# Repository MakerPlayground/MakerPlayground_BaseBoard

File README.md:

# MakerPlayground_BaseBoard
Maker Playground Base Board schematic and PCB design.

Complete the design with Kicad 5.0.2 or newer.

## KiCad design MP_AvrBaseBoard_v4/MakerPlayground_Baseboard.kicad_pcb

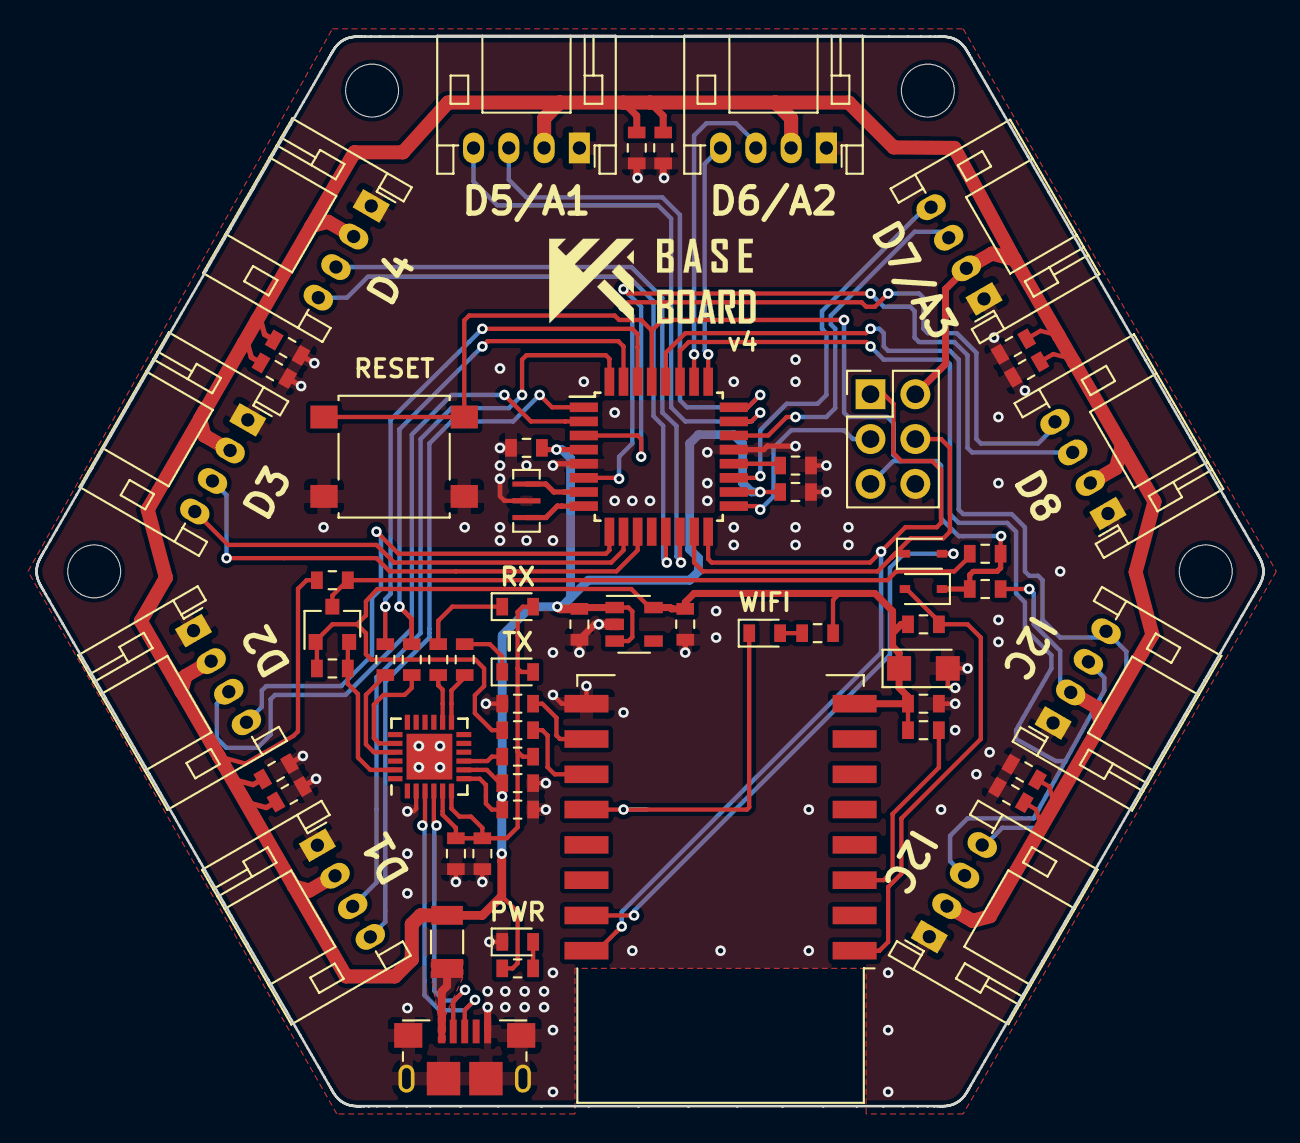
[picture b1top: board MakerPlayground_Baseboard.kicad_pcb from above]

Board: 2 copper layers, 69.5 x 60.6 mm, 63 parts (1 on the bottom side), 51 nets.

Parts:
C1, C2: 4.7uF; C_0603_1608Metric
C3, C5, C7, C11, C12, C13, C15, C16, C18, C20, C22: 0.1uF; C_0603_1608Metric
C4, C9, C17, C19, C21: 10uF; C_0603_1608Metric
C6, C8, C14: 1uF; C_0603_1608Metric
C10: 10uF; CP_EIA-3216-12_Kemet-S
D2: Green; LED_0603_1608Metric
D3, D4: Yellow; LED_0603_1608Metric
D5, D7: 1SS355VMTE-17; D_SOD-323
D6: RED; LED_0603_1608Metric
F1: 6V/0.5A; Fuse_1206_3216Metric
J2: USB_B_Micro; USB_Micro-B_Amphenol_10118193_Horizontal
J3: AVR-ISP-6; PinHeader_2x03_P2.54mm_Vertical
J4, J5, J6, J7, J8, J9, J10, J11, J13, J14: 112504RT/RH; JST_PH_S4B-PH-K_1x04_P2.00mm_Horizontal
JP1: Flashing Mode; SolderJumper-2_P1.3mm_Open_Pad1.0x1.5mm
Q2: BSS138; SOT-23
R2, R5, R6, R7, R8, R9, R14: 1K; R_0603_1608Metric
R3, R4, R10, R11, R12, R13, R15: 10K; R_0603_1608Metric
SW1: RESET; SW_SPST_B3S-1000
U2: AP2127K-3.3; SOT-23-5
U3: CP2102N-A01-GQFN24; QFN-24-1EP_4x4mm_P0.5mm_EP2.6x2.6mm
U4: ATmega328PB-MU; TQFP-32_7x7mm_P0.8mm
U5: ESP-12E; ESP-12E_ButtLess
Y1: CSTCE16M0V53-R0; Resonator_Murata_CSTCE-V-3Pin_3.2x1.3mm

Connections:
+3V3: C8.1, C10.1, C14.1, Q2.1, R3.1, R10.2, R11.1, R13.1, R14.1, U2.5, U5.8
+5V: C2.1, C4.1, C5.1, C6.1, C7.1, C9.1, C11.1, C13.1, C16.1, C17.1, C18.1, C19.1, C20.1, C21.1, C22.1, F1.1, J3.2, J4.2, J5.2, J6.2, J7.2, J8.2, J9.2, J10.2, J11.2, J13.2, J14.2, R4.1, R5.1, R15.1, U2.1, U2.3, U3.7, U3.8, U4.4, U4.18
/D+: J2.3, U3.3
/D-: J2.2, U3.4
A0: J5.4, U4.23
A1: J5.3, U4.24
A2: J8.4, U4.25
A3: J8.3, U4.26
A4: J11.4, U4.19
A5: J11.3, U4.22
D2: J4.3, U4.32
D3: J4.4, U4.1
D4: J7.3, U4.2
D5: J7.4, U4.9
D6: J10.4, U4.10
D7: J10.3, U4.11
D9: J13.4, U4.13
D10: J13.3, U4.14
D11: J14.3, U4.3
D12: J14.4, U4.6
DTR: C15.1, Q2.3, R4.2
DTR_3V3: Q2.2, R3.2, U3.23
ESP_RX: D7.1, J3.4, U4.15
ESP_TX: J3.1, U4.16, U5.22
GND: C1.2, C2.2, C3.2, C4.2, C5.2, C6.2, C7.2, C8.2, C9.2, C10.2, C11.2, C12.2, C13.2, C14.2, C16.2, C17.2, C18.2, C19.2, C20.2, C21.2, C22.2, D2.1, J2.5, J2.6, J3.6, J4.1, J5.1, J6.1, J7.1, J8.1, J9.1, J10.1, J11.1, J13.1, J14.1, JP1.2, R12.1, SW1.2, U2.2, U3.2, U3.25, U4.5, U4.21, U5.15, Y1.2
MCU_RX: R7.1, U4.30
MCU_TX: R6.1, U4.31
unnamed: C1.1, C3.1, D3.2, D4.2, R2.1, U3.5, U3.6
unnamed: C12.1, U4.20
unnamed: D2.2, R5.2
unnamed: D3.1, R8.1
unnamed: D4.1, R9.1
unnamed: D5.2, R11.2, U5.1
unnamed: D6.1, JP1.1, U5.18
unnamed: D6.2, R14.2
unnamed: D7.2, U5.21
unnamed: F1.2, J2.1
unnamed: R2.2, U3.9
unnamed: R6.2, U3.20
unnamed: R7.2, U3.21
unnamed: R8.2, U3.13
unnamed: R9.2, U3.14
unnamed: R10.1, U5.3
unnamed: R12.2, U5.16
unnamed: R13.2, U5.17
unnamed: U4.7, Y1.3
unnamed: U4.8, Y1.1
RST: C15.2, D5.1, J3.5, R15.2, SW1.1, U4.29
SCK: J3.3, U4.17
SCL0: J6.4, J9.4, U4.28
SDA0: J6.3, J9.3, U4.27

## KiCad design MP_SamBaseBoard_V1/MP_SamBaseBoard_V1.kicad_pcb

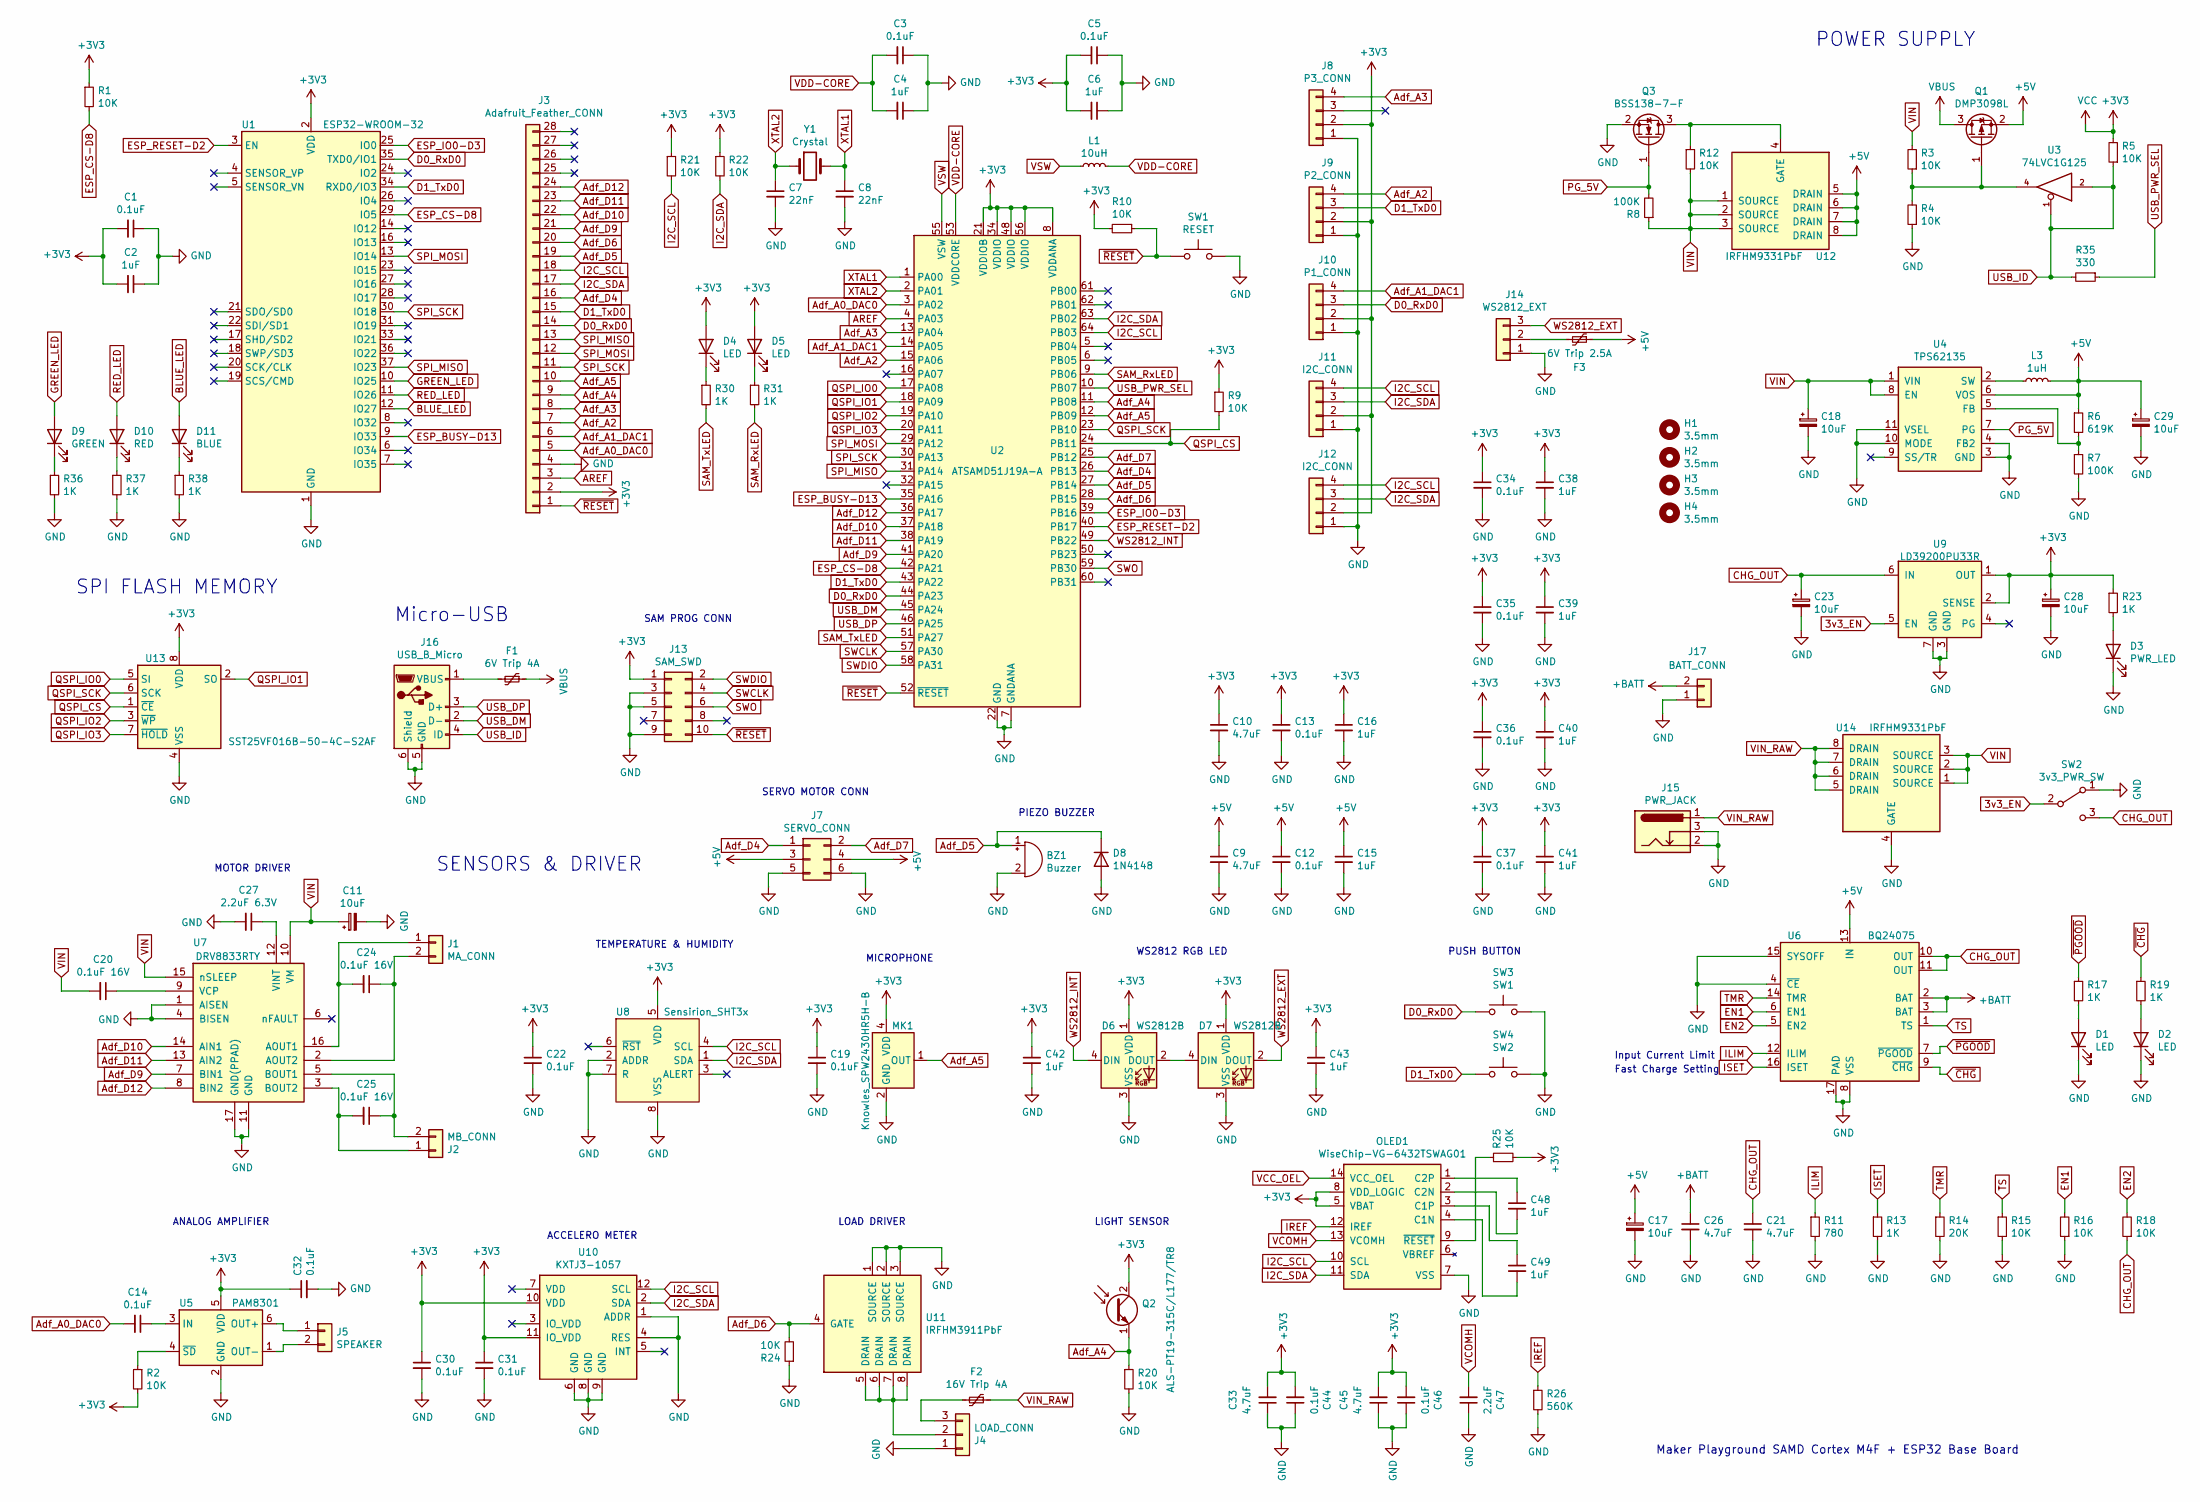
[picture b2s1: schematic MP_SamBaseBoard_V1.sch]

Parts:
BZ1: Buzzer; MagneticBuzzer_Kobitone_254-EMB84Q-RO
C1, C3, C5, C12, C13, C14, C19, C22, C30, C31, C32, C34, C35, C36, C37, C44, C46: 0.1uF; C_0603_1608Metric
C2, C4, C6, C15, C16, C38, C39, C40, C41, C42, C43, C48, C49: 1uF; C_0603_1608Metric
C7, C8: 22nF; C_0603_1608Metric; Mfg. Part 06036C223KAT2A
C9, C10, C21, C26, C33, C45: 4.7uF; C_0603_1608Metric
C11, C17, C18, C23, C28, C29: 10uF; CP_EIA-3216-12_Kemet-S
C20, C24, C25: 0.1uF 16V; C_0603_1608Metric
C27: 2.2uF 6.3V; C_0603_1608Metric
C47: 2.2uF; C_0603_1608Metric
D1, D2, D4, D5: LED; LED_0603_1608Metric
D3: PWR_LED; LED_0603_1608Metric
D6, D7: WS2812B; WS2812B_MINI
D8: 1N4148; D_SOD-323
D9: GREEN; LED_0603_1608Metric
D10: RED; LED_0603_1608Metric
D11: BLUE; LED_0603_1608Metric
F1: 6V Trip 4A; Fuse_1206_3216Metric; Mfg Part TLC-NSMD200
F2: 16V Trip 4A; Fuse_1812_4532Metric; Mfg Part SMD1812P200TF16
F3: 6V Trip 2.5A; Fuse_1812_4532Metric; Mfg Part MF-MSMF125-2
H1, H2, H3, H4: 3.5mm; MountingHole_3.5mm
J1: MA_CONN; TerminalBlock_Dinkle_ED350V_1x02_P3.50mm_Horizontal
J2: MB_CONN; TerminalBlock_Dinkle_ED350V_1x02_P3.50mm_Horizontal
J3: Adafruit_Feather_CONN; Adafruit-Feather_WoMountPoint_TypeB
J4: LOAD_CONN; TerminalBlock_Dinkle_ED350V_1x03_P3.50mm_Horizontal
J5: SPEAKER; TerminalBlock_Dinkle_ED350V_1x02_P3.50mm_Horizontal
J7: SERVO_CONN; PinHeader_2x03_P2.54mm_Vertical
J8: P3_CONN; JST_PH_B4B-PH-K_1x04_P2.00mm_Vertical
J9: P2_CONN; JST_PH_B4B-PH-K_1x04_P2.00mm_Vertical
J10: P1_CONN; JST_PH_B4B-PH-K_1x04_P2.00mm_Vertical
J11, J12: I2C_CONN; JST_PH_B4B-PH-K_1x04_P2.00mm_Vertical
J13: SAM_SWD; PinHeader_2x05_P1.27mm_Vertical
J14: WS2812_EXT; PinHeader_1x03_P2.54mm_Vertical
J15: PWR_JACK; BarrelJack_Horizontal; Mfg. Part PJ-002A; Mouser No. 490-PJ-002A
J16: USB_B_Micro; USB_Micro-B_Amphenol_10118193_Horizontal
J17: BATT_CONN; TerminalBlock_Dinkle_ED350V_1x02_P3.50mm_Horizontal
L1: 10uH; L_0805_2012Metric; Mfg. Part LQM21DH100M70L
L3: 1uH; SPM6530T; Mfg. Part SPM6530T-1R0M120
MK1: Knowles_SPW2430HR5H-B; SPW2430HR5H-B
OLED1: WiseChip-VG-6432TSWAG01
Q1: DMP3098L; SOT-23
Q2: ALS-PT19-315C/L177/TR8; D_0603_1608Metric
Q3: BSS138-7-F; SOT-23
R1, R2, R3, R4, R5, R9, R10, R12, R15, R16, R18, R20, R21, R22, R24, R25: 10K; R_0603_1608Metric
R6: 619K; R_0603_1608Metric
R7, R8: 100K; R_0603_1608Metric
R11: 780; R_0603_1608Metric
R13, R17, R19, R23, R30, R31, R36, R37, R38: 1K; R_0603_1608Metric
R14: 20K; R_0603_1608Metric
R26: 560K; R_0603_1608Metric
R35: 330; R_0603_1608Metric
SW1: RESET; SW_Push_TS-1145A-B-A
SW2: 3v3_PWR_SW; SSSS811101
SW3: SW1; SW_Push_TS-1145A-B-A
SW4: SW2; SW_Push_TS-1145A-B-A
U1: ESP32-WROOM-32; ESP32-WROOM-32_WifiNinaPin
U2: ATSAMD51J19A-A; TQFP-64_10x10mm_P0.5mm
U3: 74LVC1G125; SOT-23-5
U4: TPS62135; VQFN-HR-11
U5: PAM8301; SOT-23-6
U6: BQ24075; VQFN-16-1EP_3x3mm_P0.5mm_EP1.6x1.6mm_ThermalVias
U7: DRV8833RTY; Texas_S-PWQFN-N16_EP2.1x2.1mm_ThermalVias
U8: Sensirion_SHT3x
U9: LD39200PU33R; DFN-6-1EP_3x3mm_P0.95mm_EP1.7x2.6mm
U10: KXTJ3-1057; LGA-12_2x2mm_P0.5mm
U11: IRFHM3911PbF; PQFN_3x3mm_IRFHM3911PbF
U12, U14: IRFHM9331PbF; PQFN_3x3mm_IRFHM9331TRPbF
U13: SST25VF016B-50-4C-S2AF; SOIC-8_5.275x5.275mm_P1.27mm
Y1: Crystal; Crystal_SMD_2012-2Pin_2.0x1.2mm; Mfg. Part ABS06-127-32.768kHz-T

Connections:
3v3_EN: SW2.2 (B), U9.5 (EN)
+3V3: C1.2, C2.2, C5.2, C6.2, C10.1, C13.1, C16.1, C19.1, C22.1, C28.1, C30.1, C31.1, C32.1, C33.2, C34.1, C35.1, C36.1, C37.1, C38.1, C39.1, C40.1, C41.1, C42.1, C43.1, C44.2, C45.2, C46.2, D4.2 (A), D5.2 (A), D6.1 (VDD), D7.1 (VDD), J3.2, J8.2, J9.2, J10.2, J11.2, J12.2, J13.1, MK1.4 (VDD), OLED1.5 (VBAT), OLED1.8 (VDD_LOGIC), Q2.2 (C), R1.1, R2.2, R5.2, R9.1, R10.2, R21.1, R22.1, R23.1, R25.2, U1.2 (VDD), U2.8 (VDDANA), U2.21 (VDDIOB), U2.34 (VDDIO), U2.48 (VDDIO), U2.56 (VDDIO), U3.5 (VCC), U5.5 (VDD), U8.5 (VDD), U9.1 (OUT), U9.2 (SENSE), U10.10 (VDD), U10.11 (IO_VDD), U13.8 (VDD)
+5V: C9.1, C12.1, C15.1, C17.1, C29.1, F3.1, J7.3, J7.4, L3.2, Q1.2 (S), R6.1, U4.6 (VOS), U6.13 (IN), U12.5 (DRAIN), U12.6 (DRAIN), U12.7 (DRAIN), U12.8 (DRAIN)
+BATT: C26.1, J17.2, U6.2 (BAT), U6.3 (BAT)
AREF: J3.3, U2.4 (PA03)
Adf_A0_DAC0: C14.2, J3.5, U2.3 (PA02)
Adf_A1_DAC1: J3.6, J10.4, U2.14 (PA05)
Adf_A2: J3.7, J9.4, U2.15 (PA06)
Adf_A3: J3.8, J8.4, U2.13 (PA04)
Adf_A4: J3.9, Q2.1 (E), R20.1, U2.11 (PB08)
Adf_A5: J3.10, MK1.1 (OUT), U2.12 (PB09)
Adf_D4: J3.16, J7.1, U2.26 (PB13)
Adf_D5: BZ1.1 (-), D8.1 (K), J3.19, U2.27 (PB14)
Adf_D6: J3.20, R24.2, U2.28 (PB15), U11.4 (GATE)
Adf_D7: J7.2, U2.25 (PB12)
Adf_D9: J3.21, U2.41 (PA20), U7.7 (BIN1)
Adf_D10: J3.22, U2.37 (PA18), U7.14 (AIN1)
Adf_D11: J3.23, U2.38 (PA19), U7.13 (AIN2)
Adf_D12: J3.24, U2.36 (PA17), U7.8 (BIN2)
BLUE_LED: D11.2 (A), U1.12 (IO27)
CHG_OUT: C21.1, C23.1, R18.1, SW2.3 (C), U6.10 (OUT), U6.11 (OUT), U9.6 (IN)
D0_RxD0: J3.14, J10.3, SW3.1, U1.35 (TXD0/IO1), U2.44 (PA23)
D1_TxD0: J3.15, J9.3, SW4.1, U1.34 (RXD0/IO3), U2.43 (PA22)
EN1: R16.2, U6.6 (EN1)
EN2: R18.2, U6.5 (EN2)
ESP_BUSY-D13: U1.9 (IO33), U2.35 (PA16)
ESP_CS-D8: R1.2, U1.29 (IO5), U2.42 (PA21)
ESP_IO0-D3: U1.25 (IO0), U2.39 (PB16)
ESP_RESET-D2: U1.3 (EN), U2.40 (PB17)
GND: BZ1.2 (+), C1.1, C2.1, C3.1, C4.1, C5.1, C6.1, C7.2, C8.2, C9.2, C10.2, C11.2, C12.2, C13.2, C15.2, C16.2, C17.2, C18.2, C19.2, C21.2, C22.2, C23.2, C26.2, C27.2, C28.2, C29.2, C30.2, C31.2, C32.2, C33.1, C34.2, C35.2, C36.2, C37.2, C38.2, C39.2, C40.2, C41.2, C42.2, C43.2, C44.1, C45.1, C46.1, C47.1, D1.1 (K), D2.1 (K), D3.1 (K), D6.3 (VSS), D7.3 (VSS), D8.2 (A), J3.4, J4.1, J7.5, J7.6, J8.1, J9.1, J10.1, J11.1, J12.1, J13.3, J13.5, J13.9, J14.1, J15.2, J15.3, J16.5 (GND), J16.6 (Shield), J17.1, MK1.2 (GND), MK1.3 (GND), OLED1.7 (VSS), Q3.2 (S), R4.1, R7.2, R11.2, R13.2, R14.2, R15.2, R16.1, R20.2, R24.1, R26.2, R36.2, R37.2, R38.2, SW1.2, SW2.1 (A), SW3.2, SW4.2, U1.1 (GND), U1.15 (GND), U1.38 (GND), U1.39 (GND), U2.7 (GNDANA), U2.22 (GND), U2.33 (GND), U2.47 (GND), U2.54 (GND), U3.3 (GND), U4.3 (GND), U4.4 (FB2), U4.10 (MODE), U4.11 (VSEL), U5.2 (GND), U6.4 (~CE), U6.8 (VSS), U6.15 (SYSOFF), U6.17 (PAD), U7.1 (AISEN), U7.4 (BISEN), U7.11 (GND), U7.17 (GND(PPAD)), U8.2 (ADDR), U8.7 (R), U8.8 (VSS), U8.9 (PAD), U9.3 (GND), U9.7 (GND), U10.1 (ADDR), U10.4 (RES), U10.6 (GND), U10.8 (GND), U10.9 (GND), U11.1 (SOURCE), U11.2 (SOURCE), U11.3 (SOURCE), U13.4 (VSS), U14.4 (GATE)
GREEN_LED: D9.2 (A), U1.10 (IO25)
I2C_SCL: J3.18, J11.4, J12.4, OLED1.10 (SCL), R21.2, U2.64 (PB03), U8.4 (SCL), U10.12 (SCL)
I2C_SDA: J3.17, J11.3, J12.3, OLED1.11 (SDA), R22.2, U2.63 (PB02), U8.1 (SDA), U10.2 (SDA)
ILIM: R11.1, U6.12 (ILIM)
IREF: OLED1.12 (IREF), R26.1
ISET: R13.1, U6.16 (ISET)
unnamed: C14.1, U5.3 (IN)
unnamed: C20.1, U7.9 (VCP)
unnamed: C24.1, J1.2, U7.2 (AOUT2)
unnamed: C24.2, J1.1, U7.16 (AOUT1)
unnamed: C25.1, J2.2, U7.5 (BOUT1)
unnamed: C25.2, J2.1, U7.3 (BOUT2)
unnamed: C27.1, U7.12 (VINT)
unnamed: C48.1, OLED1.1 (C2P)
unnamed: C48.2, OLED1.2 (C2N)
unnamed: C49.1, OLED1.3 (C1P)
unnamed: C49.2, OLED1.4 (C1N)
unnamed: D1.2 (A), R17.2
unnamed: D2.2 (A), R19.2
unnamed: D3.2 (A), R23.2
unnamed: D4.1 (K), R30.1
unnamed: D5.1 (K), R31.1
unnamed: D6.2 (DOUT), D7.4 (DIN)
unnamed: D9.1 (K), R36.1
unnamed: D10.1 (K), R37.1
unnamed: D11.1 (K), R38.1
unnamed: F1.2, J16.1 (VBUS)
unnamed: F2.2, J4.3
unnamed: F3.2, J14.2
unnamed: J4.2, U11.5 (DRAIN), U11.6 (DRAIN), U11.7 (DRAIN), U11.8 (DRAIN)
unnamed: J5.1, U5.6 (OUT+)
unnamed: J5.2, U5.1 (OUT-)
unnamed: L3.1, U4.2 (SW)
unnamed: OLED1.9 (~RESET), R25.1
unnamed: Q1.1 (G), R3.1, R4.2, U3.4
unnamed: Q3.3 (D), R12.1, U12.4 (GATE)
unnamed: R2.1, U5.4 (~SD)
unnamed: R6.2, R7.1, U4.5 (FB)
PG_5V: Q3.1 (G), R8.2, U4.7 (PG)
QSPI_CS: R9.2, U2.24 (PB11), U13.1 (~CE)
QSPI_IO0: U2.17 (PA08), U13.5 (SI)
QSPI_IO1: U2.18 (PA09), U13.2 (SO)
QSPI_IO2: U2.19 (PA10), U13.3 (~WP~)
QSPI_IO3: U2.20 (PA11), U13.7 (~HOLD~)
QSPI_SCK: U2.23 (PB10), U13.6 (SCK)
RED_LED: D10.2 (A), U1.11 (IO26)
SAM_RxLED: R31.2, U2.9 (PB06)
SAM_TxLED: R30.2, U2.51 (PA27)
SPI_MISO: J3.13, U1.37 (IO23), U2.31 (PA14)
SPI_MOSI: J3.12, U1.13 (IO14), U2.29 (PA12)
SPI_SCK: J3.11, U1.30 (IO18), U2.30 (PA13)
SWCLK: J13.4, U2.57 (PA30)
SWDIO: J13.2, U2.58 (PA31)
SWO: J13.6, U2.59 (PB30)
TMR: R14.1, U6.14 (TMR)
TS: R15.1, U6.1 (TS)
USB_DM: J16.2 (D-), U2.45 (PA24)
USB_DP: J16.3 (D+), U2.46 (PA25)
USB_ID: J16.4 (ID), R5.1, R35.2, U3.1, U3.2
USB_PWR_SEL: R35.1, U2.10 (PB07)
VBUS: F1.1, Q1.3 (D)
VCOMH: C47.2, OLED1.13 (VCOMH)
VDD-CORE: C3.2, C4.2, L1.2, U2.53 (VDDCORE)
VIN: C11.1, C18.1, C20.2, R3.2, R8.1, R12.2, U4.1 (VIN), U4.8 (EN), U7.10 (VM), U7.15 (nSLEEP), U12.1 (SOURCE), U12.2 (SOURCE), U12.3 (SOURCE), U14.1 (SOURCE), U14.2 (SOURCE), U14.3 (SOURCE)
VIN_RAW: F2.1, J15.1, U14.5 (DRAIN), U14.6 (DRAIN), U14.7 (DRAIN), U14.8 (DRAIN)
VSW: L1.1, U2.55 (VSW)
WS2812_EXT: D7.2 (DOUT), J14.3
WS2812_INT: D6.4 (DIN), U2.49 (PB22)
XTAL1: C8.1, U2.1 (PA00), Y1.2
XTAL2: C7.1, U2.2 (PA01), Y1.1
~CHG: R19.1, U6.9 (~CHG)
~PGOOD: R17.1, U6.7 (~PGOOD)
~RESET: J3.1, J13.10, R10.1, SW1.1, U2.52 (~RESET)

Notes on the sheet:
POWER SUPPLY
SENSORS & DRIVER
ACCELERO METER
TEMPERATURE & HUMIDITY
MOTOR DRIVER
ANALOG AMPLIFIER
LOAD DRIVER
MICROPHONE
Maker Playground SAMD Cortex M4F + ESP32 Base Board
PIEZO BUZZER
SPI FLASH MEMORY
Fast Charge Setting
Input Current Limit
Micro-USB
SERVO MOTOR CONN
SAM PROG CONN
WS2812 RGB LED
LIGHT SENSOR
PUSH BUTTON

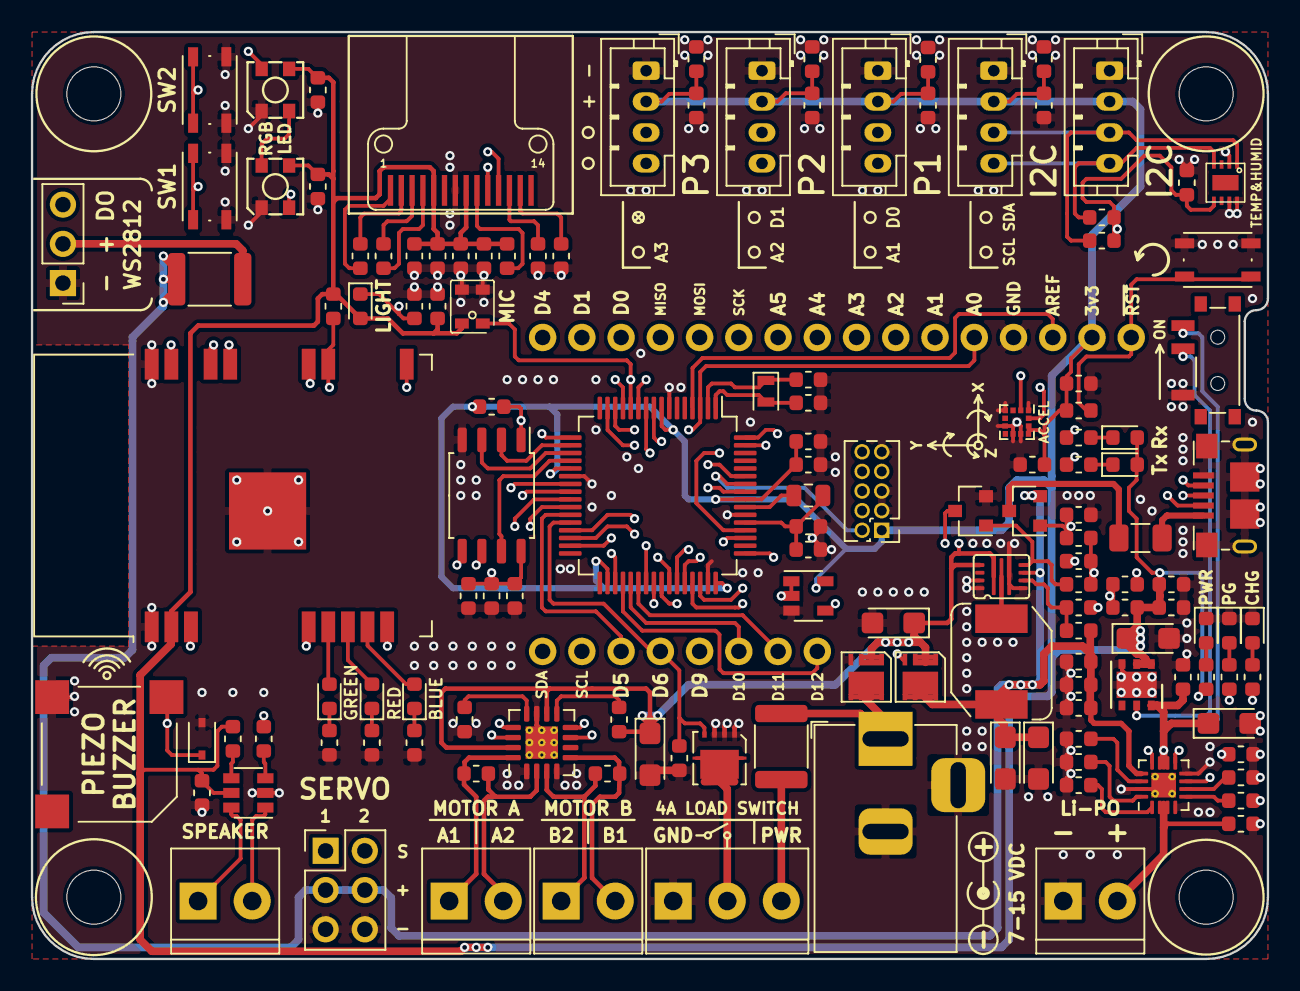
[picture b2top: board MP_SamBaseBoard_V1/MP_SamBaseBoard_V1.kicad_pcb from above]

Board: 4 copper layers, 80.0 x 60.0 mm, 142 parts (0 on the bottom side), 103 nets.

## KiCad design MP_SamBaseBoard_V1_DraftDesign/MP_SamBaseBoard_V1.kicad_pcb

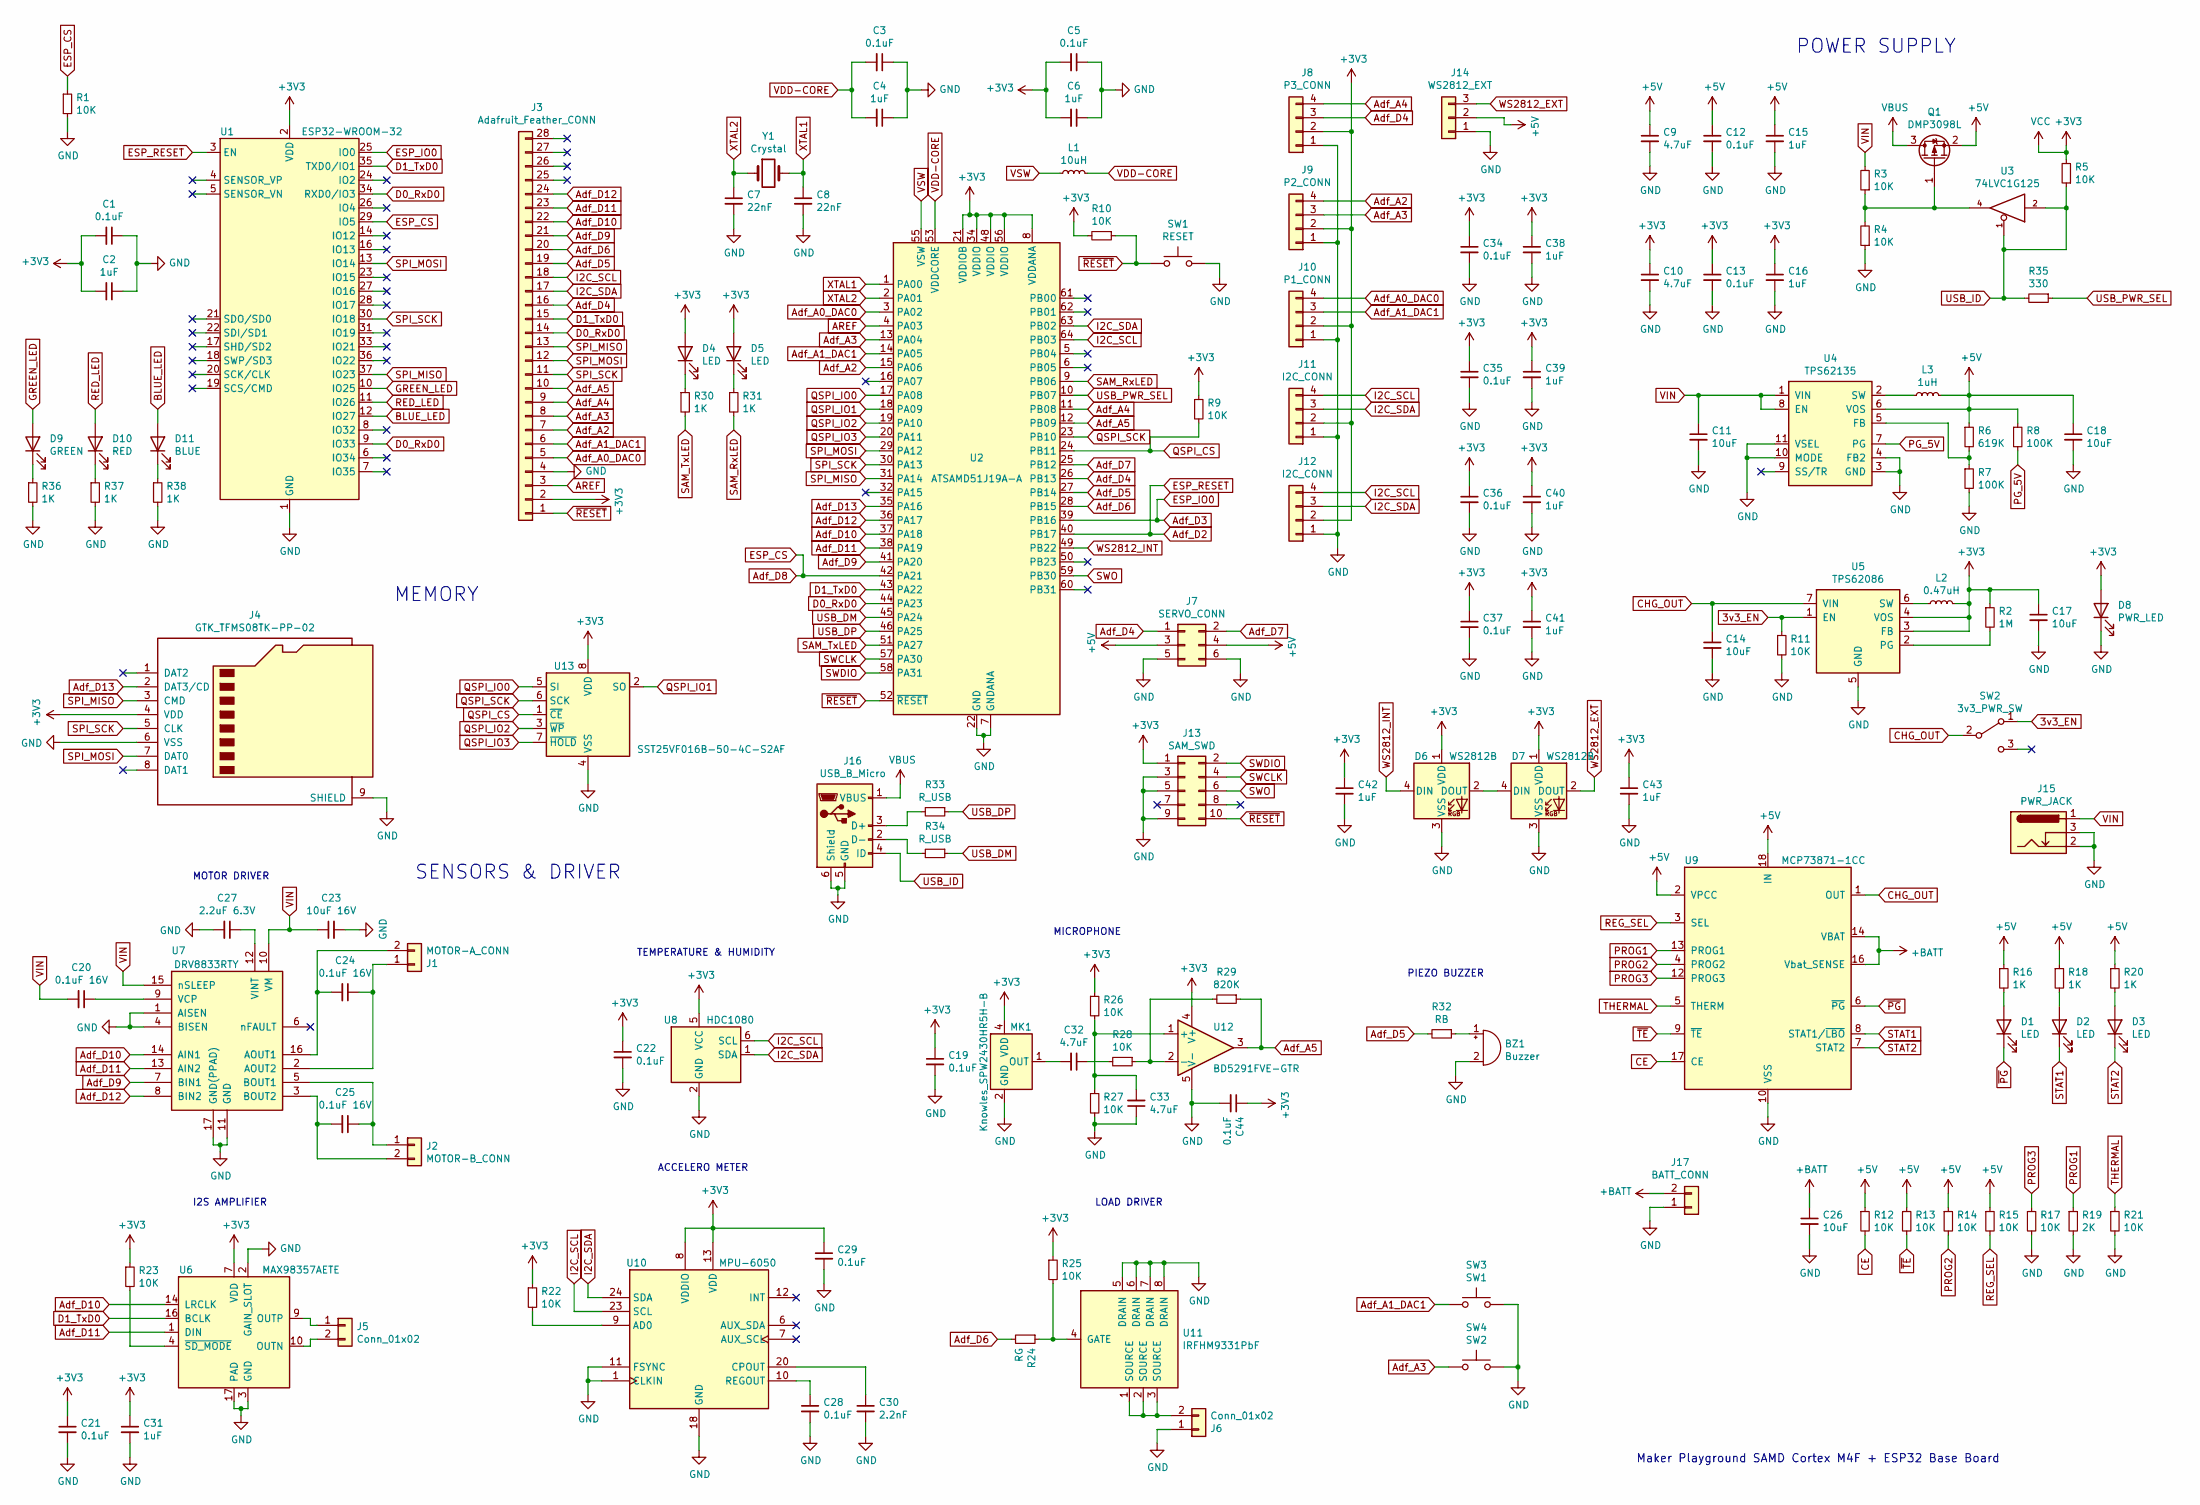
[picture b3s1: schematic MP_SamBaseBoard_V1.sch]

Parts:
BZ1: Buzzer; MagneticBuzzer_Kobitone_254-EMB84Q-RO
C1, C3, C5, C12, C13, C19, C21, C22, C28, C29, C34, C35, C36, C37, C44: 0.1uF; C_0603_1608Metric
C2, C4, C6, C15, C16, C31, C38, C39, C40, C41, C42, C43: 1uF; C_0603_1608Metric
C7, C8: 22nF; C_0603_1608Metric; Mfg. Part 06036C223KAT2A
C9, C10, C32, C33: 4.7uF; C_0603_1608Metric
C11, C14, C17, C18, C26: 10uF; CP_EIA-3216-12_Kemet-S
C20, C24, C25: 0.1uF 16V; C_0603_1608Metric
C23: 10uF 16V; CP_EIA-3216-12_Kemet-S
C27: 2.2uF 6.3V; C_0603_1608Metric
C30: 2.2nF; C_0603_1608Metric
D1, D2, D3, D4, D5: LED; LED_0603_1608Metric
D6, D7: WS2812B; WS2812B_MINI
D8: PWR_LED; LED_0603_1608Metric
D9: GREEN; LED_0603_1608Metric
D10: RED; LED_0603_1608Metric
D11: BLUE; LED_0603_1608Metric
J1: MOTOR-A_CONN; DINKLE_EK500V-2P
J2: MOTOR-B_CONN; DINKLE_EK500V-2P
J3: Adafruit_Feather_CONN; Adafruit-Feather_WoMountPoint_TypeB
J4: GTK_TFMS08TK-PP-02
J5: Conn_01x02; TerminalBlock_Dinkle_ED350V_1x02_P3.50mm_Horizontal
J6: Conn_01x02; DINKLE_EK500V-2P
J7: SERVO_CONN; PinHeader_2x03_P2.54mm_Vertical
J8: P3_CONN; JST_PH_B4B-PH-K_1x04_P2.00mm_Vertical
J9: P2_CONN; JST_PH_B4B-PH-K_1x04_P2.00mm_Vertical
J10: P1_CONN; JST_PH_B4B-PH-K_1x04_P2.00mm_Vertical
J11, J12: I2C_CONN; JST_PH_B4B-PH-K_1x04_P2.00mm_Vertical
J13: SAM_SWD; PinHeader_2x05_P1.27mm_Vertical
J14: WS2812_EXT; PinHeader_1x03_P2.54mm_Vertical
J15: PWR_JACK; BarrelJack_Horizontal; Mfg. Part DS-012-B-PBT-ROHS
J16: USB_B_Micro; USB_Micro-B_Amphenol_10118193_Horizontal
J17: BATT_CONN; TerminalBlock_Dinkle_ED350V_1x02_P3.50mm_Horizontal
L1: 10uH; L_0805_2012Metric; Mfg. Part LQM21DH100M70L
L2: 0.47uH; L_0806_2016Metric; Mfg. Part 74479976147A
L3: 1uH; L_1616_2020Metric; Mfg. Part IHLP2020CZER1R0M01
MK1: Knowles_SPW2430HR5H-B; SPW2430HR5H-B
Q1: DMP3098L; SOT-23
R1, R3, R4, R5, R9, R10, R11, R12, R13, R14, R15, R17, R21, R22, R23, R25, R26, R27, R28: 10K; R_0603_1608Metric
R2: 1M; R_0603_1608Metric
R6: 619K; R_0603_1608Metric
R7, R8: 100K; R_0603_1608Metric
R16, R18, R20, R30, R31, R36, R37, R38: 1K; R_0603_1608Metric
R19: 2K; R_0603_1608Metric
R24: RG; R_0603_1608Metric
R29: 820K; R_0603_1608Metric
R32: RB; R_0603_1608Metric
R33, R34: R_USB; R_0603_1608Metric
R35: 330; R_0603_1608Metric
SW1: RESET; SW_SPST_B3S-1000
SW2: 3v3_PWR_SW; SW_SPDT_CK-JS102011JCQN
SW3: SW1; SW_SPST_B3S-1000
SW4: SW2; SW_SPST_B3S-1000
U1: ESP32-WROOM-32; ESP32-WROOM-32_WifiNinaPin
U2: ATSAMD51J19A-A; TQFP-64_10x10mm_P0.5mm
U3: 74LVC1G125; SOT-23-5
U4: TPS62135; VQFN-HR-11
U5: TPS62086; Texas_VSON7
U6: MAX98357AETE; TQFN-16-1EP_3x3mm_P0.5mm_EP1.23x1.23mm
U7: DRV8833RTY; Texas_S-PWQFN-N16_EP2.1x2.1mm_ThermalVias
U8: HDC1080; Texas_PWSON-N6
U9: MCP73871-1CC; QFN-20-1EP_4x4mm_P0.5mm_EP2.5x2.5mm
U10: MPU-6050; InvenSense_QFN-24_4x4mm_P0.5mm
U11: IRFHM9331PbF; PQFN_3x3mm
U12: BD5291FVE-GTR; SOT-353_SC-70-5
U13: SST25VF016B-50-4C-S2AF; SOIC-8_5.275x5.275mm_P1.27mm
Y1: Crystal; Crystal_SMD_2012-2Pin_2.0x1.2mm; Mfg. Part ABS06-127-32.768kHz-T

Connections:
3v3_EN: R11.1, SW2.1 (A), U5.1 (EN)
+3V3: C1.2, C2.2, C5.2, C6.2, C10.1, C13.1, C16.1, C17.1, C19.1, C21.1, C22.1, C29.1, C31.1, C34.1, C35.1, C36.1, C37.1, C38.1, C39.1, C40.1, C41.1, C42.1, C43.1, C44.1, D4.2 (A), D5.2 (A), D6.1 (VDD), D7.1 (VDD), D8.2 (A), J3.2, J4.4 (VDD), J8.2, J9.2, J10.2, J11.2, J12.2, J13.1, L2.2, MK1.4 (VDD), R2.1, R5.2, R9.1, R10.2, R22.1, R23.1, R25.1, R26.1, U1.2 (VDD), U2.8 (VDDANA), U2.21 (VDDIOB), U2.34 (VDDIO), U2.48 (VDDIO), U2.56 (VDDIO), U3.5 (VCC), U5.3 (FB), U5.4 (VOS), U6.7 (VDD), U6.8 (VDD), U8.5 (VCC), U10.8 (VDDIO), U10.13 (VDD), U12.4 (V+), U13.8 (VDD)
+5V: C9.1, C12.1, C15.1, C18.1, J7.3, J7.4, J14.2, L3.2, Q1.2 (S), R6.1, R8.1, R12.1, R13.1, R14.1, R15.1, R16.1, R18.1, R20.1, U4.6 (VOS), U9.2 (VPCC), U9.18 (IN), U9.19 (IN)
+BATT: C26.1, J17.2, U9.14 (VBAT), U9.15 (VBAT), U9.16 (Vbat_SENSE)
AREF: J3.3, U2.4 (PA03)
Adf_A0_DAC0: J3.5, J10.4, U2.3 (PA02)
Adf_A1_DAC1: J3.6, J10.3, SW3.1, U2.14 (PA05)
Adf_A2: J3.7, J9.4, U2.15 (PA06)
Adf_A3: J3.8, J9.3, SW4.1, U2.13 (PA04)
Adf_A4: J3.9, J8.4, U2.11 (PB08)
Adf_A5: J3.10, R29.1, U2.12 (PB09), U12.3
Adf_D2: U1.3 (EN), U2.40 (PB17)
Adf_D3: U1.25 (IO0), U2.39 (PB16)
Adf_D4: J3.16, J7.1, J8.3, U2.26 (PB13)
Adf_D5: J3.19, R32.2, U2.27 (PB14)
Adf_D6: J3.20, R24.2, U2.28 (PB15)
Adf_D7: J7.2, U2.25 (PB12)
Adf_D8: R1.1, U1.29 (IO5), U2.42 (PA21)
Adf_D9: J3.21, U2.41 (PA20), U7.7 (BIN1)
Adf_D10: J3.22, U2.37 (PA18), U6.14 (LRCLK), U7.14 (AIN1)
Adf_D11: J3.23, U2.38 (PA19), U6.1 (DIN), U7.13 (AIN2)
Adf_D12: J3.24, U2.36 (PA17), U7.8 (BIN2)
Adf_D13: J4.2 (DAT3/CD), U2.35 (PA16)
BLUE_LED: D11.2 (A), U1.12 (IO27)
CE: R12.2, U9.17 (CE)
CHG_OUT: C14.1, SW2.2 (B), U5.7 (VIN), U9.1 (OUT), U9.20 (OUT)
D0_RxD0: J3.14, U1.9 (IO33), U1.34 (RXD0/IO3), U2.44 (PA23)
D1_TxD0: J3.15, U1.35 (TXD0/IO1), U2.43 (PA22), U6.16 (BCLK)
GND: BZ1.2 (+), C1.1, C2.1, C3.1, C4.1, C5.1, C6.1, C7.2, C8.2, C9.2, C10.2, C11.2, C12.2, C13.2, C14.2, C15.2, C16.2, C17.2, C18.2, C19.2, C21.2, C22.2, C23.2, C26.2, C27.2, C28.2, C29.2, C30.2, C31.2, C33.1, C34.2, C35.2, C36.2, C37.2, C38.2, C39.2, C40.2, C41.2, C42.2, C43.2, C44.2, D6.3 (VSS), D7.3 (VSS), D8.1 (K), J3.4, J4.6 (VSS), J4.9 (SHIELD), J6.1, J7.5, J7.6, J8.1, J9.1, J10.1, J11.1, J12.1, J13.3, J13.5, J13.9, J14.1, J15.2, J15.3, J16.5 (GND), J16.6 (Shield), J17.1, MK1.2 (GND), MK1.3 (GND), R1.2, R4.1, R7.2, R11.2, R17.2, R19.2, R21.2, R27.2, R36.2, R37.2, R38.2, SW1.2, SW3.2, SW4.2, U1.1 (GND), U1.15 (GND), U1.38 (GND), U1.39 (GND), U2.7 (GNDANA), U2.22 (GND), U2.33 (GND), U2.47 (GND), U2.54 (GND), U3.3 (GND), U4.3 (GND), U4.4 (FB2), U4.10 (MODE), U4.11 (VSEL), U5.5 (GND), U6.2 (GAIN_SLOT), U6.3 (GND), U6.11 (GND), U6.15 (GND), U6.17 (PAD), U7.1 (AISEN), U7.4 (BISEN), U7.11 (GND), U7.17 (GND(PPAD)), U8.2 (GND), U9.10 (VSS), U9.11 (VSS), U9.21 (VSS), U10.1 (CLKIN), U10.11 (FSYNC), U10.18 (GND), U11.5 (DRAIN), U11.6 (DRAIN), U11.7 (DRAIN), U11.8 (DRAIN), U12.5 (V-), U13.4 (VSS)
GREEN_LED: D9.2 (A), U1.10 (IO25)
I2C_SCL: J3.18, J11.4, J12.4, U2.64 (PB03), U8.6 (SCL), U10.23 (SCL)
I2C_SDA: J3.17, J11.3, J12.3, U2.63 (PB02), U8.1 (SDA), U10.24 (SDA)
unnamed: BZ1.1 (-), R32.1
unnamed: C20.1, U7.9 (VCP)
unnamed: C24.1, J1.1, U7.2 (AOUT2)
unnamed: C24.2, J1.2, U7.16 (AOUT1)
unnamed: C25.1, J2.1, U7.5 (BOUT1)
unnamed: C25.2, J2.2, U7.3 (BOUT2)
unnamed: C27.1, U7.12 (VINT)
unnamed: C28.1, U10.10 (REGOUT)
unnamed: C30.1, U10.20 (CPOUT)
unnamed: C32.1, R28.2
unnamed: C32.2, MK1.1 (OUT)
unnamed: C33.2, R26.2, R27.1, U12.1 (+)
unnamed: D1.2 (A), R16.2
unnamed: D2.2 (A), R18.2
unnamed: D3.2 (A), R20.2
unnamed: D4.1 (K), R30.1
unnamed: D5.1 (K), R31.1
unnamed: D6.2 (DOUT), D7.4 (DIN)
unnamed: D9.1 (K), R36.1
unnamed: D10.1 (K), R37.1
unnamed: D11.1 (K), R38.1
unnamed: J5.1, U6.9 (OUTP)
unnamed: J5.2, U6.10 (OUTN)
unnamed: J6.2, U11.1 (SOURCE), U11.2 (SOURCE), U11.3 (SOURCE)
unnamed: J16.2 (D-), R34.2
unnamed: J16.3 (D+), R33.2
unnamed: L2.1, U5.6 (SW)
unnamed: L3.1, U4.2 (SW)
unnamed: Q1.1 (G), R3.1, R4.2, U3.4
unnamed: R2.2, U5.2 (PG)
unnamed: R6.2, R7.1, U4.5 (FB)
unnamed: R22.2, U10.9 (AD0)
unnamed: R23.2, U6.4 (~SD_MODE)
unnamed: R24.1, R25.2, U11.4 (GATE)
unnamed: R28.1, R29.2, U12.2 (-)
unnamed: U6.5, U6.6, U6.12, U6.13
PG_5V: R8.2, U4.7 (PG)
PROG1: R19.1, U9.13 (PROG1)
PROG2: R14.2, U9.4 (PROG2)
PROG3: R17.1, U9.12 (PROG3)
QSPI_CS: R9.2, U2.24 (PB11), U13.1 (~CE)
QSPI_IO0: U2.17 (PA08), U13.5 (SI)
QSPI_IO1: U2.18 (PA09), U13.2 (SO)
QSPI_IO2: U2.19 (PA10), U13.3 (~WP~)
QSPI_IO3: U2.20 (PA11), U13.7 (~HOLD~)
QSPI_SCK: U2.23 (PB10), U13.6 (SCK)
RED_LED: D10.2 (A), U1.11 (IO26)
REG_SEL: R15.2, U9.3 (SEL)
SAM_RxLED: R31.2, U2.9 (PB06)
SAM_TxLED: R30.2, U2.51 (PA27)
SPI_MISO: J3.13, J4.3 (CMD), U1.37 (IO23), U2.31 (PA14)
SPI_MOSI: J3.12, J4.7 (DAT0), U1.13 (IO14), U2.29 (PA12)
SPI_SCK: J3.11, J4.5 (CLK), U1.30 (IO18), U2.30 (PA13)
STAT1: D2.1 (K), U9.8 (STAT1/~LBO~)
STAT2: D3.1 (K), U9.7 (STAT2)
SWCLK: J13.4, U2.57 (PA30)
SWDIO: J13.2, U2.58 (PA31)
SWO: J13.6, U2.59 (PB30)
THERMAL: R21.1, U9.5 (THERM)
USB_DM: R34.1, U2.45 (PA24)
USB_DP: R33.1, U2.46 (PA25)
USB_ID: J16.4 (ID), R5.1, R35.2, U3.1, U3.2
USB_PWR_SEL: R35.1, U2.10 (PB07)
VBUS: J16.1 (VBUS), Q1.3 (D)
VDD-CORE: C3.2, C4.2, L1.2, U2.53 (VDDCORE)
VIN: C11.1, C20.2, C23.1, J15.1, R3.2, U4.1 (VIN), U4.8 (EN), U7.10 (VM), U7.15 (nSLEEP)
VSW: L1.1, U2.55 (VSW)
WS2812_EXT: D7.2 (DOUT), J14.3
WS2812_INT: D6.4 (DIN), U2.49 (PB22)
XTAL1: C8.1, U2.1 (PA00), Y1.2
XTAL2: C7.1, U2.2 (PA01), Y1.1
~PG: D1.1 (K), U9.6 (~PG~)
~RESET: J3.1, J13.10, R10.1, SW1.1, U2.52 (~RESET)
~TE: R13.2, U9.9 (~TE)

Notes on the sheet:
POWER SUPPLY
SENSORS & DRIVER
ACCELERO METER
TEMPERATURE & HUMIDITY
MOTOR DRIVER
I2S AMPLIFIER
LOAD DRIVER
MICROPHONE
Maker Playground SAMD Cortex M4F + ESP32 Base Board
PIEZO BUZZER
MEMORY

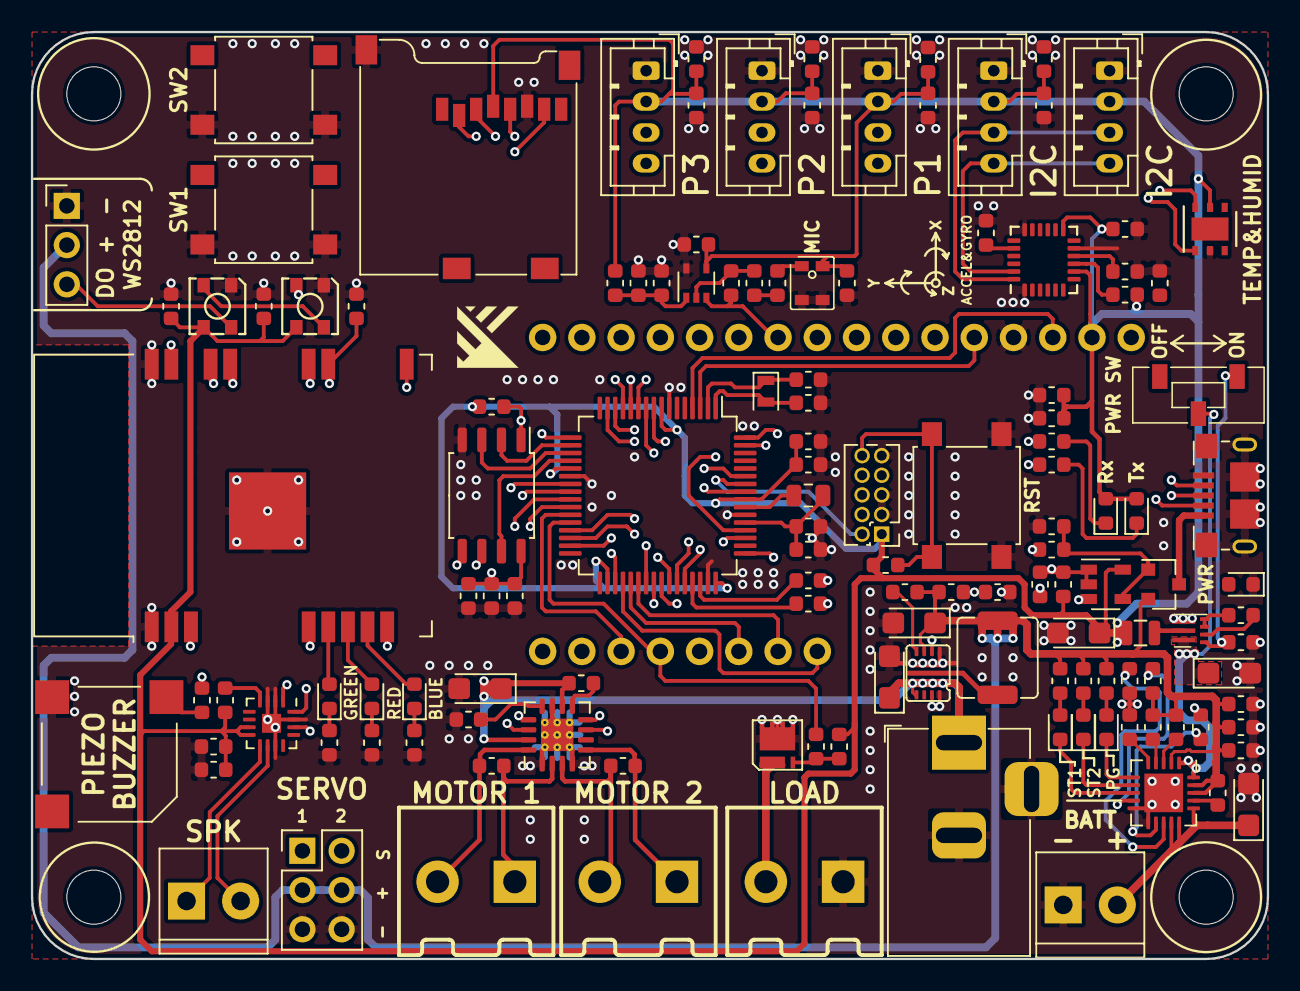
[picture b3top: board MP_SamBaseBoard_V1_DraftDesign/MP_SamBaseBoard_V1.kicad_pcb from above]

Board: 4 copper layers, 80.0 x 60.0 mm, 134 parts (0 on the bottom side), 106 nets.
